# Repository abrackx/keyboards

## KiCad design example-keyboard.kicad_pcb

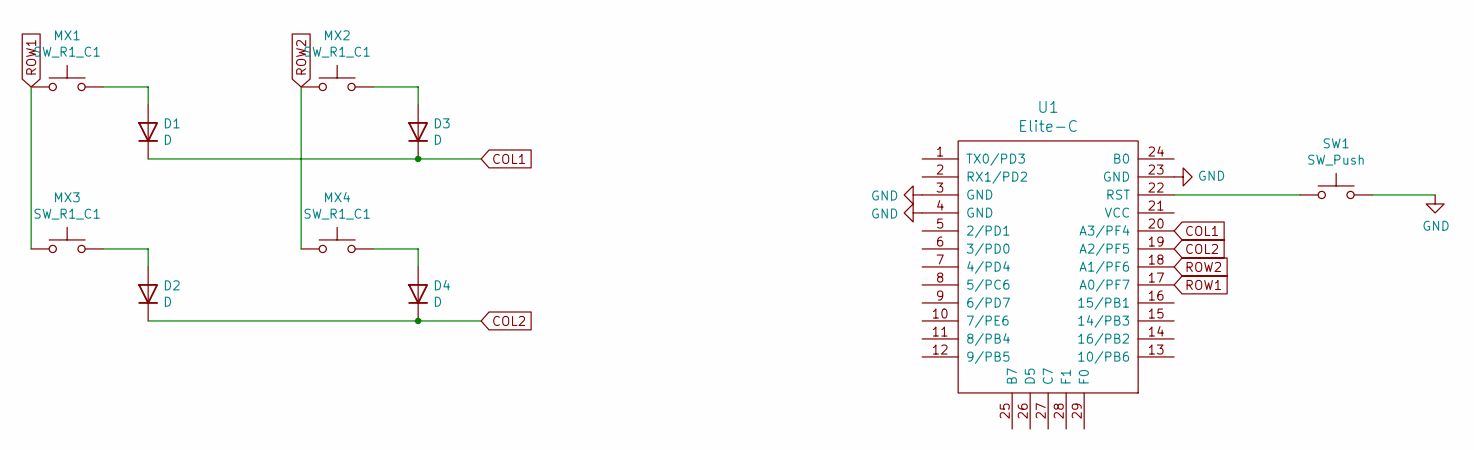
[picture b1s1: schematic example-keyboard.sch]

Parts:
D1, D2, D3, D4: D; Diode
MX1, MX2, MX3, MX4: SW_R1_C1; SW_Cherry_MX_1.00u_PCB
SW1: SW_Push; SW_PUSH_6mm_H7.3mm
U1: Elite-C

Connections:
COL1: D1.1 (K), D3.1 (K), U1.20 (A3/PF4)
COL2: D2.1 (K), D4.1 (K), U1.19 (A2/PF5)
GND: SW1.2, U1.3 (GND), U1.4 (GND), U1.23 (GND)
unnamed: D1.2 (A), MX1.2
unnamed: D2.2 (A), MX3.2
unnamed: D3.2 (A), MX2.2
unnamed: D4.2 (A), MX4.2
unnamed: SW1.1, U1.22 (RST)
ROW1: MX1.1, MX3.1, U1.17 (A0/PF7)
ROW2: MX2.1, MX4.1, U1.18 (A1/PF6)

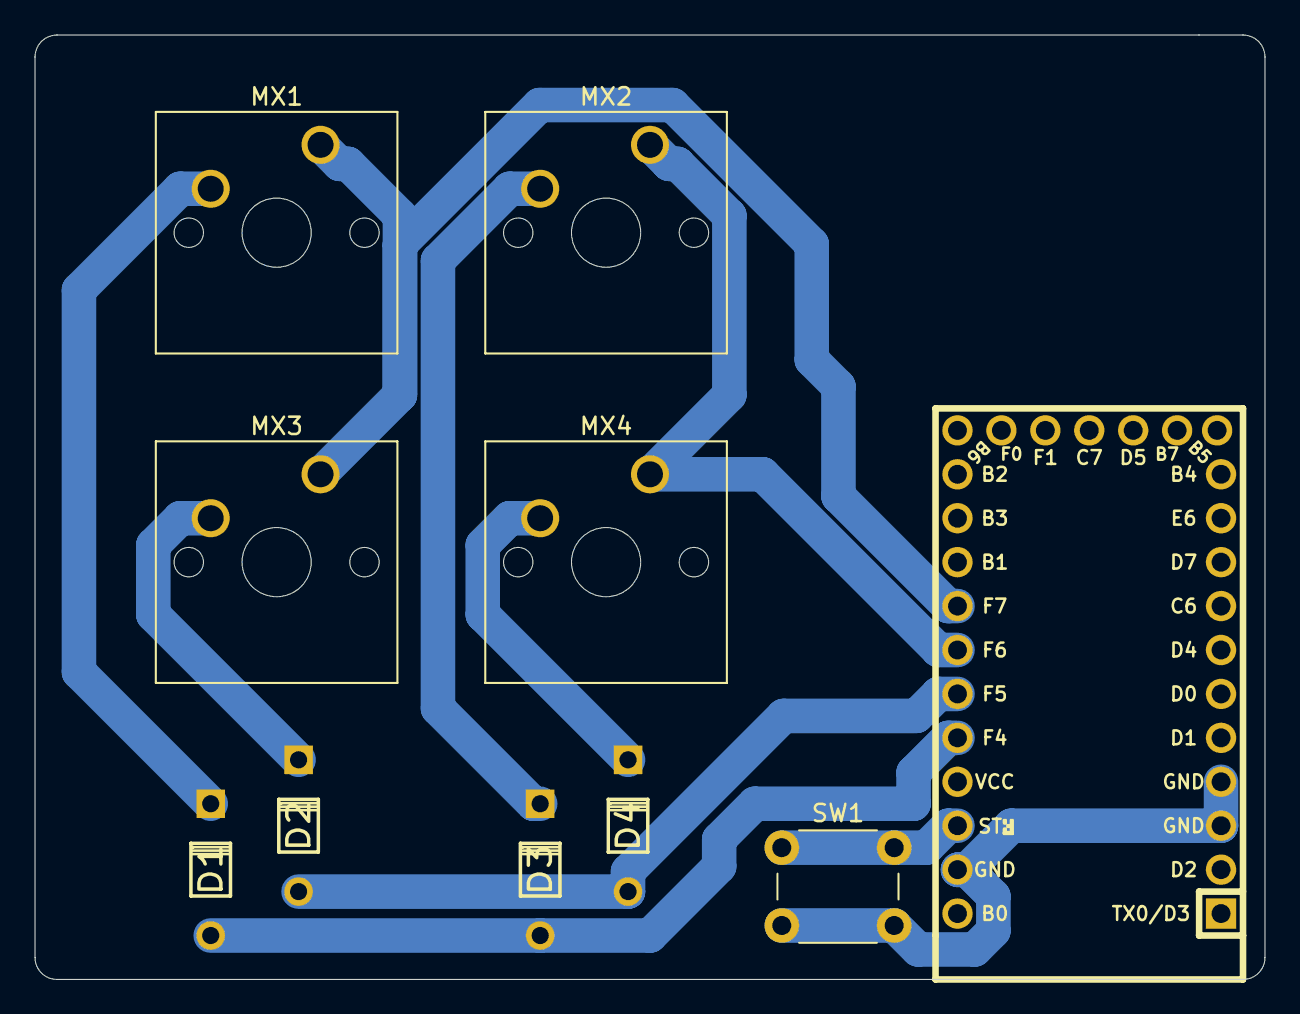
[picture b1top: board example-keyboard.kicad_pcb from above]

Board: 2 copper layers, 71.1 x 54.6 mm, 10 parts (0 on the bottom side), 10 nets.

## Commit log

2020-07-28 Initialize KiCad project
2020-07-28 Adds ai03 libs
2020-10-23 Adds initial elite c based macro pad schematic and keebio lib/symbols
2020-10-23 Creates pcb layout
2020-10-23 Adds edge cuts
2020-10-24 better layout
2020-10-24 Adds routing that I think works but I changed the pins that the rows/columns are talking to so that may bite me
2020-10-24 Adds logo (who knew it would be this difficult to make an svg look good on a board)
2020-10-24 Creates gerbers. Ordered pcb but realized the logo was upside down. Oops.
2020-11-08 cleans up directory
2020-11-08 Adds keebio libs <3
2020-11-28 Adds v2
